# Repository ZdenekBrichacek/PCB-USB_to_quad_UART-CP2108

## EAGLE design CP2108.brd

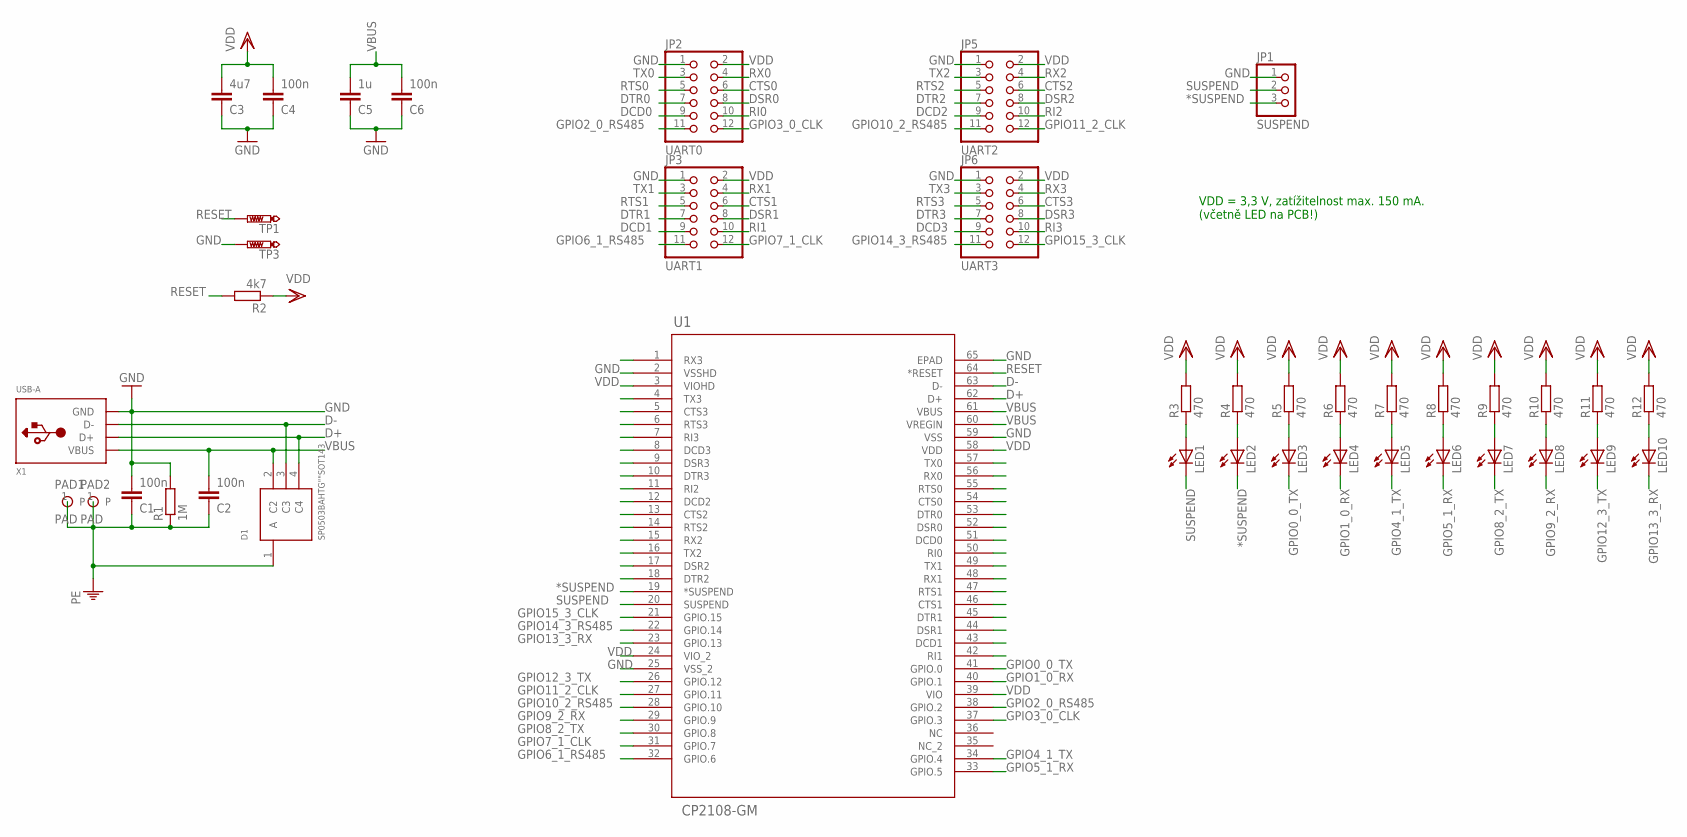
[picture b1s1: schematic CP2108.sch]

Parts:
C1, C2, C4, C6: 100n; C0603
C3: 4u7; C0805
C5: 1u; C0805
D1: SP0503BAHTG""SOT143; SOT143
JP1: SUSPEND; 1X03
JP2: UART0; 2X06
JP3: UART1; 2X06
JP5: UART2; 2X06
JP6: UART3; 2X06
LED1, LED2, LED3, LED4, LED5, LED6, LED7, LED8, LED9, LED10: LEDSML0603; SML0603
PAD1, PAD2: PAD; PAD3
R1: 1M; R0603
R2: 4k7; R0603
R3, R4, R5, R6, R7, R8, R9, R10, R11, R12: 470; R0603
TP1: RESET; B1,27
TP3: GND; B1,27
U1: CP2108-GM; QFN64
X1: USB-A; MOLEX_480371000

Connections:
*SUSPEND: JP1.3, LED2.C, U1.19 (*SUSPEND)
CTS0: JP2.6, U1.54 (CTS0)
CTS1: JP3.6, U1.46 (CTS1)
CTS2: JP5.6, U1.13 (CTS2)
CTS3: JP6.6, U1.5 (CTS3)
D+: D1.4 (C4), U1.62 (D+), X1.3 (D+)
D-: D1.3 (C3), U1.63 (D-), X1.2 (D-)
DCD0: JP2.9, U1.51 (DCD0)
DCD1: JP3.9, U1.43 (DCD1)
DCD2: JP5.9, U1.12 (DCD2)
DCD3: JP6.9, U1.8 (DCD3)
DSR0: JP2.8, U1.52 (DSR0)
DSR1: JP3.8, U1.44 (DSR1)
DSR2: JP5.8, U1.17 (DSR2)
DSR3: JP6.8, U1.9 (DSR3)
DTR0: JP2.7, U1.53 (DTR0)
DTR1: JP3.7, U1.45 (DTR1)
DTR2: JP5.7, U1.18 (DTR2)
DTR3: JP6.7, U1.10 (DTR3)
GND: C1.2, C3.1, C4.1, C5.1, C6.1, JP1.1, JP2.1, JP3.1, JP5.1, JP6.1, R1.2, TP3.TP, U1.2 (VSSHD), U1.25 (VSS_2), U1.59 (VSS), U1.65 (EPAD), X1.4 (GND)
GPIO0_0_TX: LED3.C, U1.41 (GPIO.0)
GPIO1_0_RX: LED4.C, U1.40 (GPIO.1)
GPIO2_0_RS485: JP2.11, U1.38 (GPIO.2)
GPIO3_0_CLK: JP2.12, U1.37 (GPIO.3)
GPIO4_1_TX: LED5.C, U1.34 (GPIO.4)
GPIO5_1_RX: LED6.C, U1.33 (GPIO.5)
GPIO6_1_RS485: JP3.11, U1.32 (GPIO.6)
GPIO7_1_CLK: JP3.12, U1.31 (GPIO.7)
GPIO8_2_TX: LED7.C, U1.30 (GPIO.8)
GPIO9_2_RX: LED8.C, U1.29 (GPIO.9)
GPIO10_2_RS485: JP5.11, U1.28 (GPIO.10)
GPIO11_2_CLK: JP5.12, U1.27 (GPIO.11)
GPIO12_3_TX: LED9.C, U1.26 (GPIO.12)
GPIO13_3_RX: LED10.C, U1.23 (GPIO.13)
GPIO14_3_RS485: JP6.11, U1.22 (GPIO.14)
GPIO15_3_CLK: JP6.12, U1.21 (GPIO.15)
unnamed: LED2.A, R4.1
unnamed: LED5.A, R7.1
unnamed: LED1.A, R3.1
unnamed: LED3.A, R5.1
unnamed: LED6.A, R8.1
unnamed: LED7.A, R9.1
unnamed: LED8.A, R10.1
unnamed: LED9.A, R11.1
unnamed: LED10.A, R12.1
unnamed: LED4.A, R6.1
RESET: R2.2, TP1.TP, U1.64 (*RESET)
RI0: JP2.10, U1.50 (RI0)
RI1: JP3.10, U1.42 (RI1)
RI2: JP5.10, U1.11 (RI2)
RI3: JP6.10, U1.7 (RI3)
RTS0: JP2.5, U1.55 (RTS0)
RTS1: JP3.5, U1.47 (RTS1)
RTS2: JP5.5, U1.14 (RTS2)
RTS3: JP6.5, U1.6 (RTS3)
RX0: JP2.4, U1.56 (RX0)
RX1: JP3.4, U1.48 (RX1)
RX2: JP5.4, U1.15 (RX2)
RX3: JP6.4, U1.1 (RX3)
SHIELD: C1.1, C2.1, D1.1 (A), PAD1.1, PAD2.1, R1.1
SUSPEND: JP1.2, LED1.C, U1.20 (SUSPEND)
TX0: JP2.3, U1.57 (TX0)
TX1: JP3.3, U1.49 (TX1)
TX2: JP5.3, U1.16 (TX2)
TX3: JP6.3, U1.4 (TX3)
VBUS: C2.2, C5.2, C6.2, D1.2 (C2), U1.60 (VREGIN), U1.61 (VBUS), X1.1 (VBUS)
VDD: C3.2, C4.2, JP2.2, JP3.2, JP5.2, JP6.2, R2.1, R3.2, R4.2, R5.2, R6.2, R7.2, R8.2, R9.2, R10.2, R11.2, R12.2, U1.3 (VIOHD), U1.24 (VIO_2), U1.39 (VIO), U1.58 (VDD)

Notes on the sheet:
VDD = 3,3 V, zatížitelnost max. 150 mA. (včetně LED na PCB!)

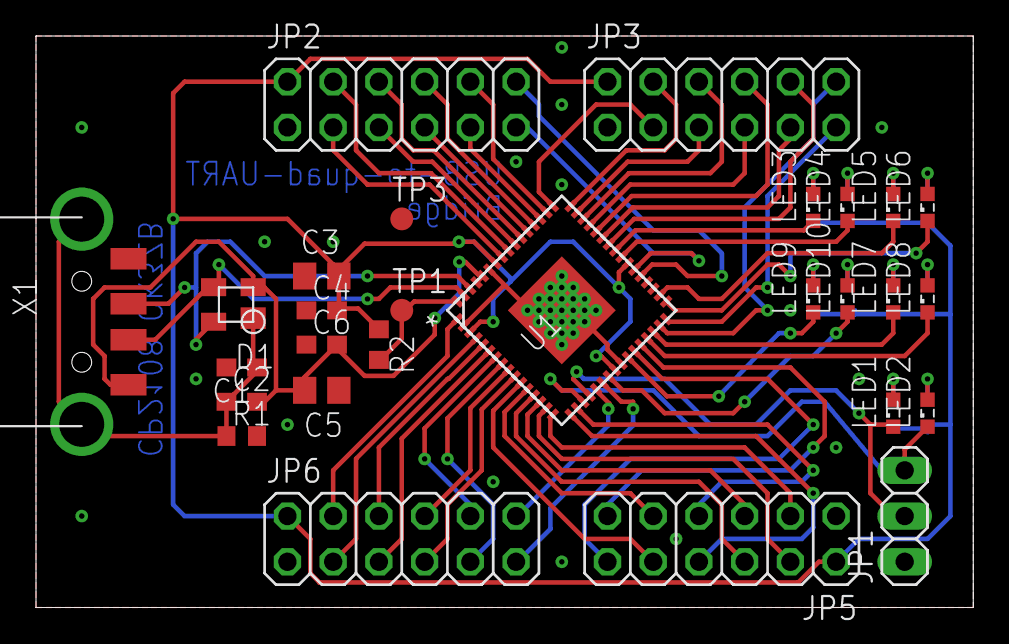
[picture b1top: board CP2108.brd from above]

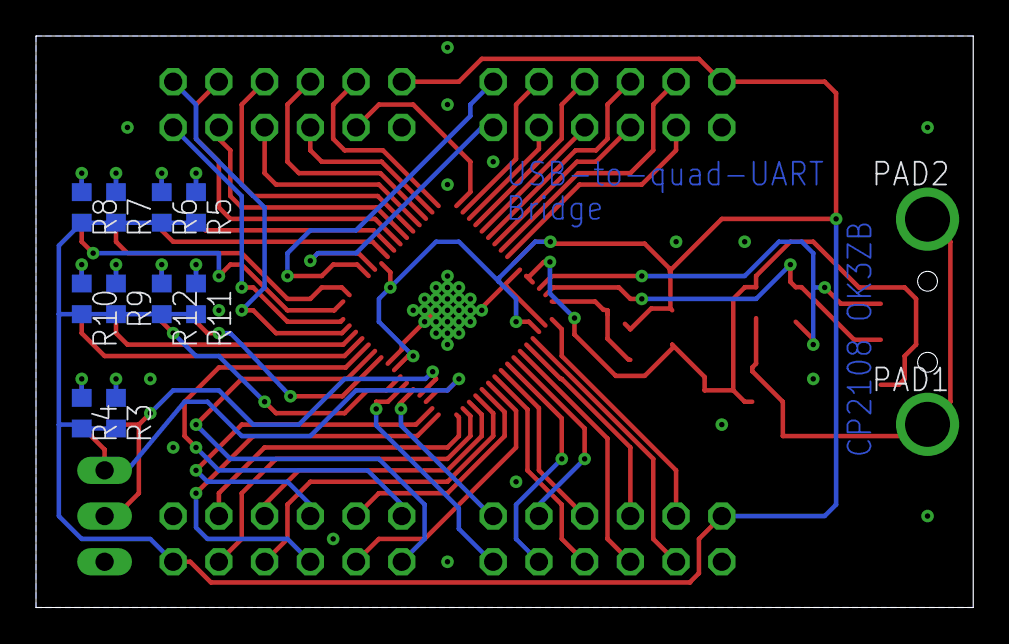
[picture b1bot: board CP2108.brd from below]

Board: 2 copper layers, 52.1 x 31.8 mm, 40 parts (10 on the bottom side), 67 nets.

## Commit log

2017-10-10 :space_invader: Added .gitattributes & .gitignore files
2017-10-10 Initial version
